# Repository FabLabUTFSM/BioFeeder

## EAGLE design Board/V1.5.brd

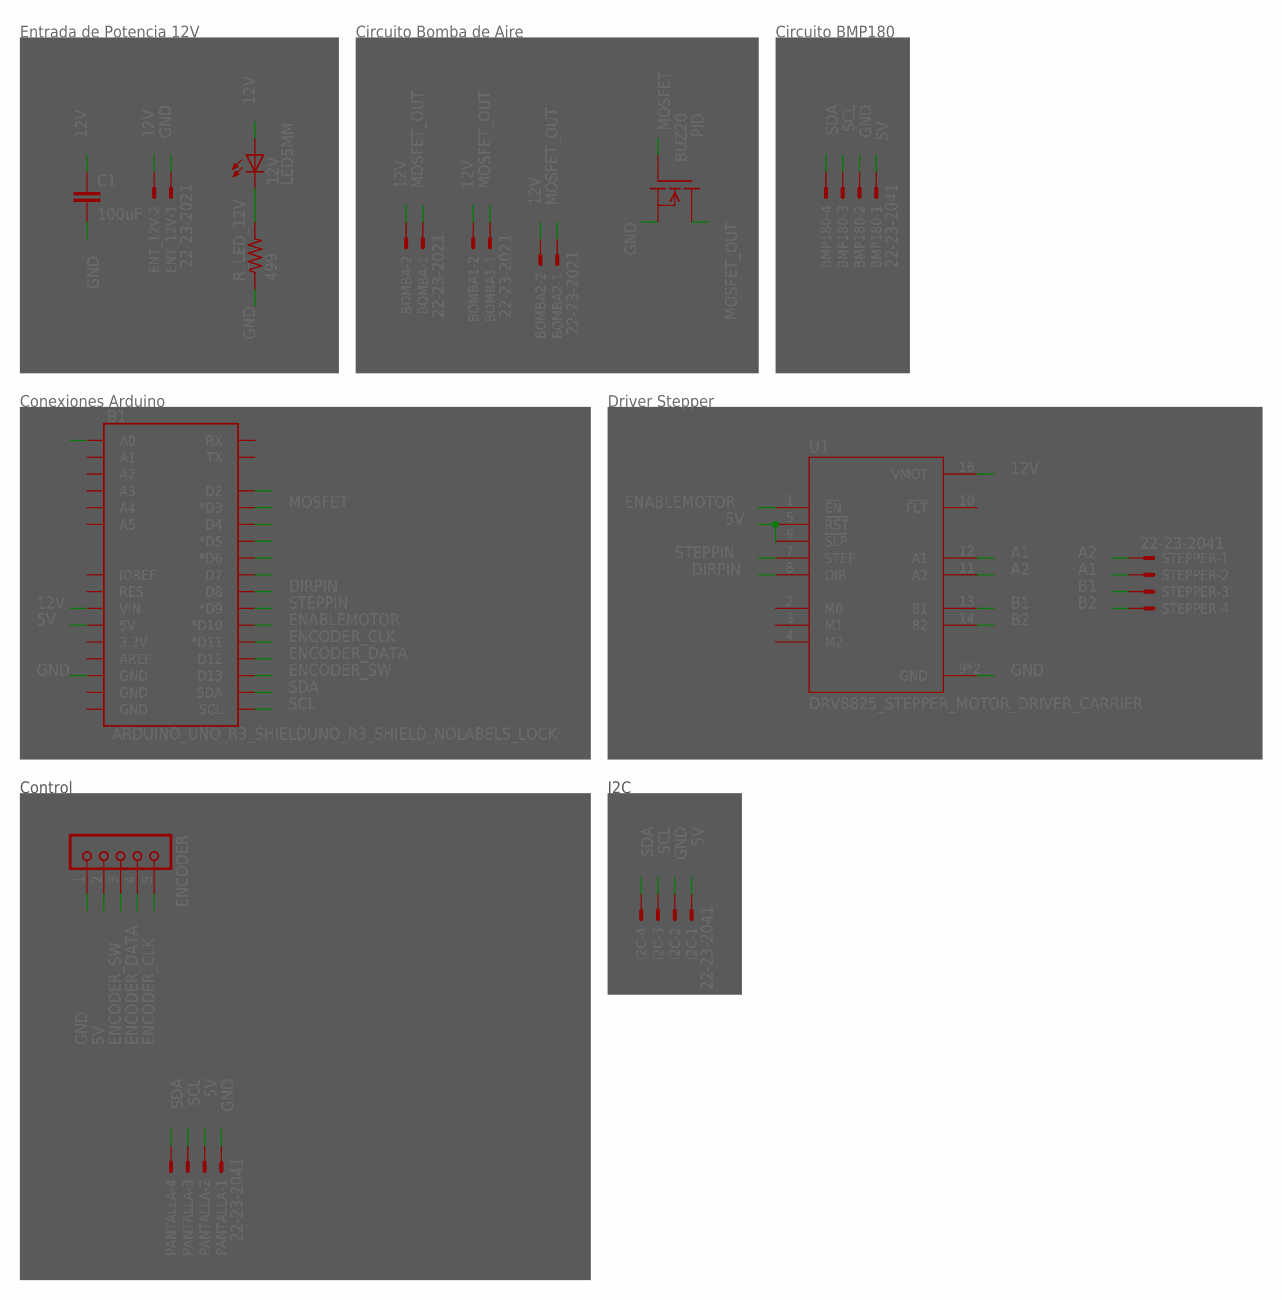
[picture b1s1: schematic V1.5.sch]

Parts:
12V: LED5MM; 5MM
B1: ARDUINO_UNO_R3_SHIELDUNO_R3_SHIELD_NOLABELS_LOCK; UNO_R3_SHIELD_NOLABELS_LOCK
BMP180: 22-23-2041
BOMBA, BOMBA1, BOMBA2: 22-23-2021
C1: 100uF; C2.5-5
ENCODER: JU05
ENT_12V: 22-23-2021
I2C: 22-23-2041
PANTALLA: 22-23-2041
PID: BUZ20; TO220
R_LED_12V: 499; 0204/7
STEPPER: 22-23-2041
U1: DRV8825_STEPPER_MOTOR_DRIVER_CARRIER; IC_DRV8825_STEPPER_MOTOR_DRIVER_CARRIER

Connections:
5V: B1.5V, BMP180.1, ENCODER.2, I2C.1, PANTALLA.2, U1.5 (!RST), U1.6 (!SLP)
12V: 12V.IN (A), B1.VIN, BOMBA.2, BOMBA1.2, BOMBA2.2, C1.1, ENT_12V.2, U1.16 (VMOT)
A1: STEPPER.2, U1.12 (A1)
A2: STEPPER.1, U1.11 (A2)
B1: STEPPER.3, U1.13 (B1)
B2: STEPPER.4, U1.14 (B2)
BUTTON: B1.D2
DIRPIN: B1.D8, U1.8 (DIR)
ENABLEMOTOR: B1.D10 (*D10), U1.1 (!EN)
ENCODER_CLK: B1.D11 (*D11), ENCODER.5
ENCODER_DATA: B1.D12, ENCODER.4
ENCODER_SW: B1.D13, ENCODER.3
GND: B1.GND@2 (GND), BMP180.2, C1.2, ENCODER.1, ENT_12V.1, I2C.2, PANTALLA.1, PID.3 (S), R_LED_12V.1, U1.9 (GND), U1.15 (GND)
MOSFET: B1.D3 (*D3), PID.1 (G)
MOSFET_OUT: BOMBA.1, BOMBA1.1, BOMBA2.1, PID.2 (D)
unnamed: 12V.OUT (C), R_LED_12V.2
POT: B1.A0
SCL: B1.SCL, BMP180.3, I2C.3, PANTALLA.3
SDA: B1.SDA, BMP180.4, I2C.4, PANTALLA.4
STEPPIN: B1.D9 (*D9), U1.7 (STEP)

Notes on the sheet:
Entrada de Potencia 12V
Circuito Bomba de Aire
Circuito BMP180
Conexiones Arduino
Driver Stepper
Control
I2C

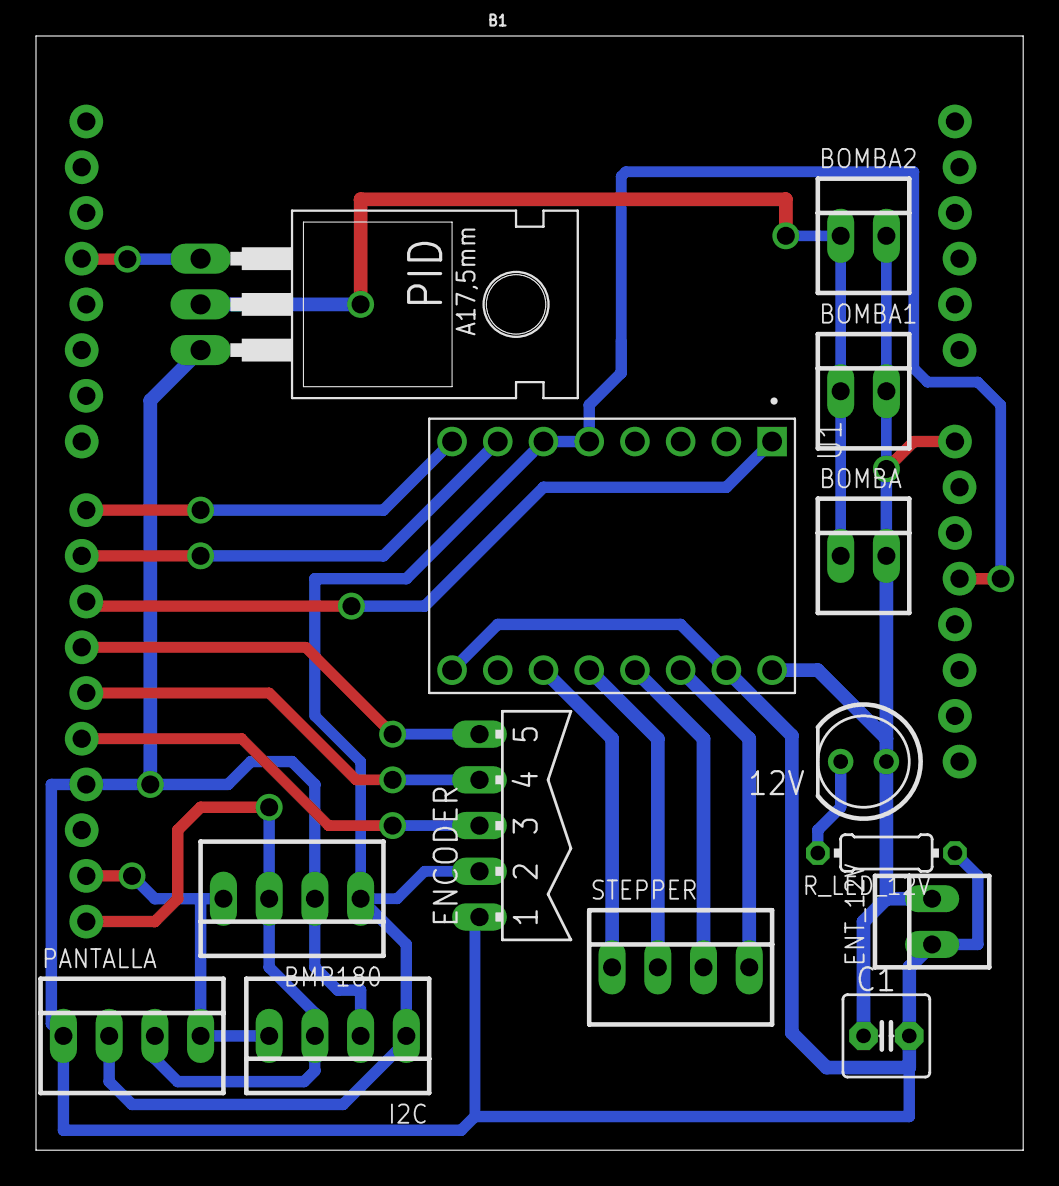
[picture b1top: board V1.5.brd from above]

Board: 2 copper layers, 54.8 x 61.9 mm, 15 parts (0 on the bottom side), 18 nets.

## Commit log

2020-07-06 Marlin + OLed ready
2020-07-07 encoder habilitado
2020-07-08 3d printer buffer contruction
2020-07-10 Encoder + I2C listo, Oled pendiente
2020-07-19 Update main

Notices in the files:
parts and their libraries:
SparkFun-Boards: Licensing: Creative Commons ShareAlike 4.0 International - https://creativecommons.org/licenses/by-sa/4.0
